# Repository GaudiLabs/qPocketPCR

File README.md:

# qPocketPCR
Quantitative PCR machine detecting fluorescence using a camera

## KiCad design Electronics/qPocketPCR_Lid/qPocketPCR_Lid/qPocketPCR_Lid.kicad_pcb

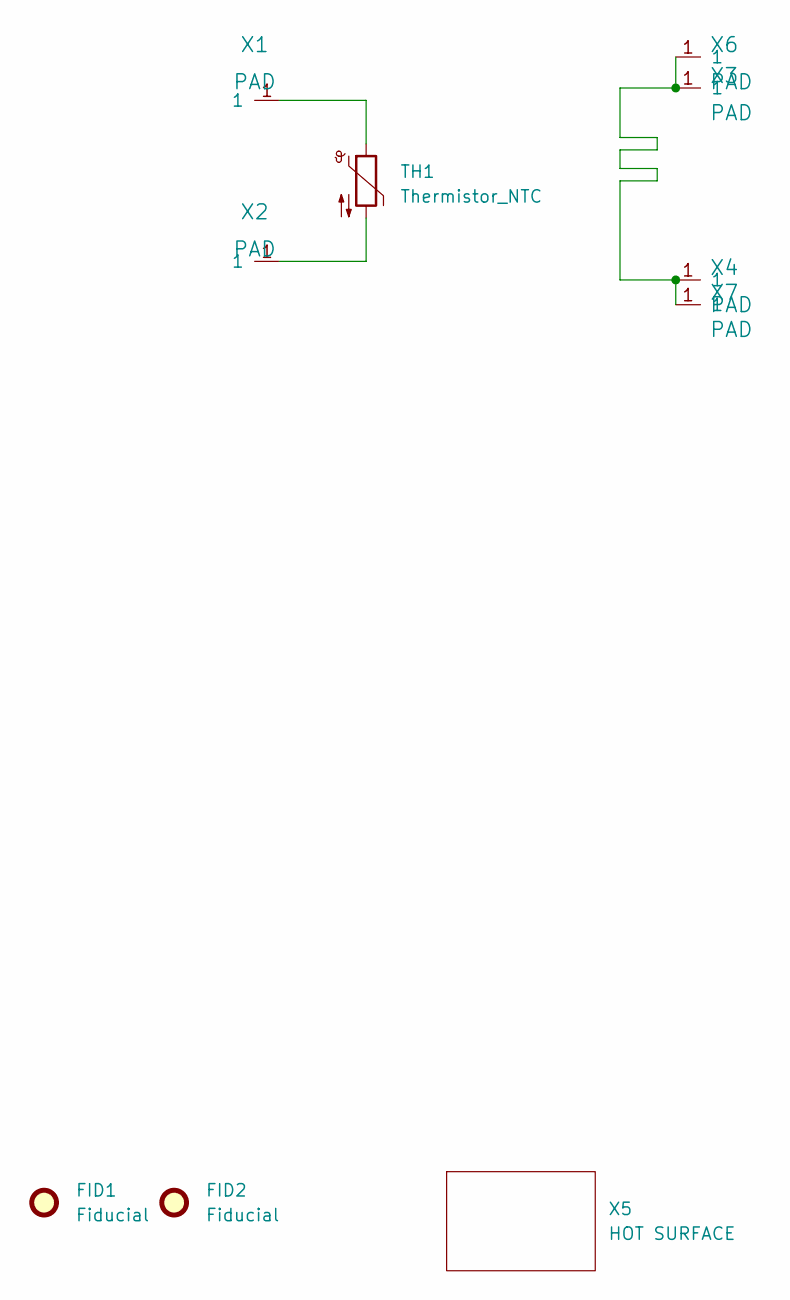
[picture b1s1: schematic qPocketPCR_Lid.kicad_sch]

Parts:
FID1, FID2: Fiducial; Fiducial_0.5mm_Mask1mm
TH1: Thermistor_NTC; R_0402_1005Metric
X1, X2, X3, X4, X6, X7: PAD; PAD_SMD_FFC
X5: HOT SURFACE; HotSurfaceWarning

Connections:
unnamed: TH1.1, X1.1
unnamed: TH1.2, X2.1
unnamed: X3.1, X4.1, X6.1, X7.1

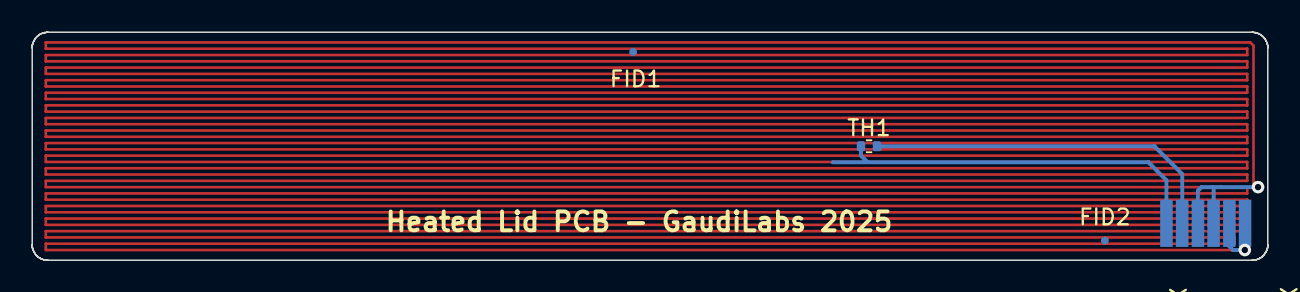
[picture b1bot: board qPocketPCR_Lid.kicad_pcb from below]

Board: 2 copper layers, 78.6 x 14.5 mm, 10 parts (9 on the bottom side), 3 nets.

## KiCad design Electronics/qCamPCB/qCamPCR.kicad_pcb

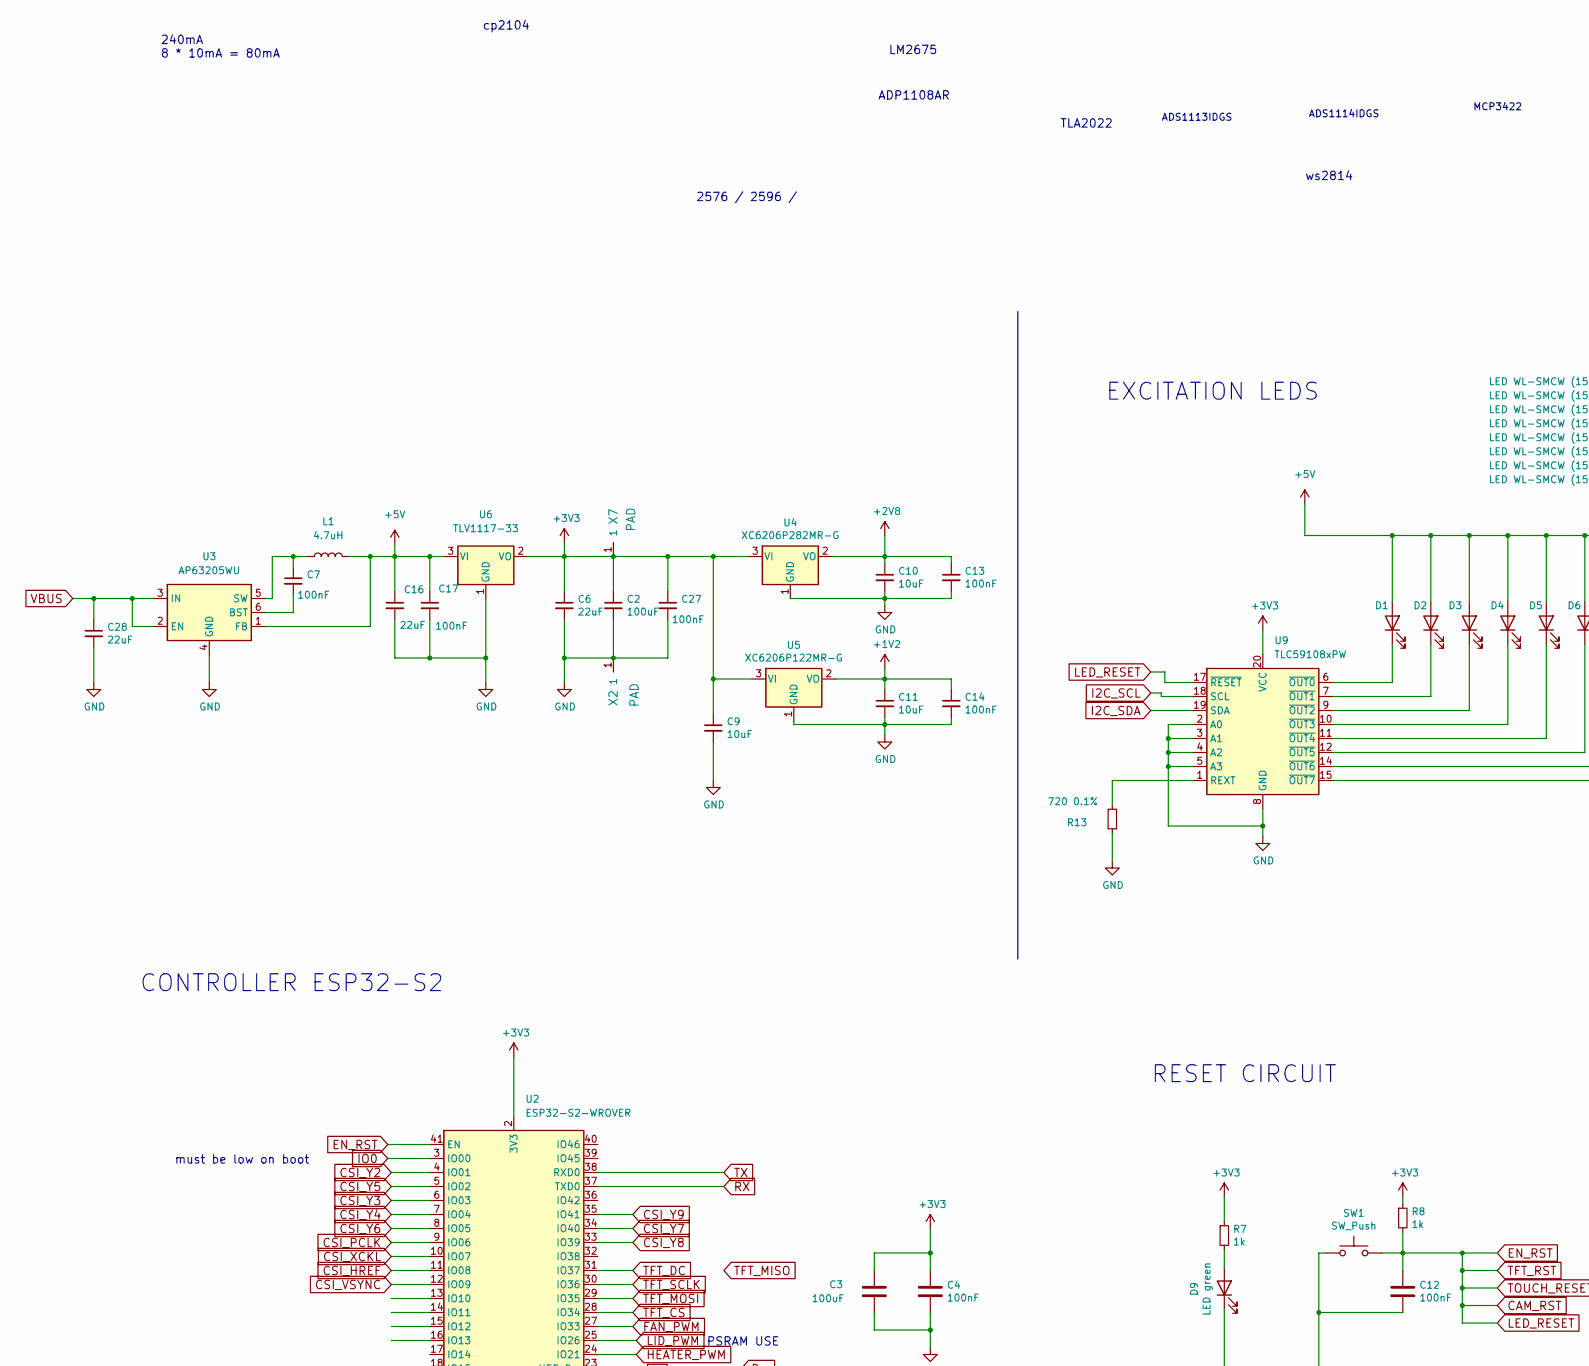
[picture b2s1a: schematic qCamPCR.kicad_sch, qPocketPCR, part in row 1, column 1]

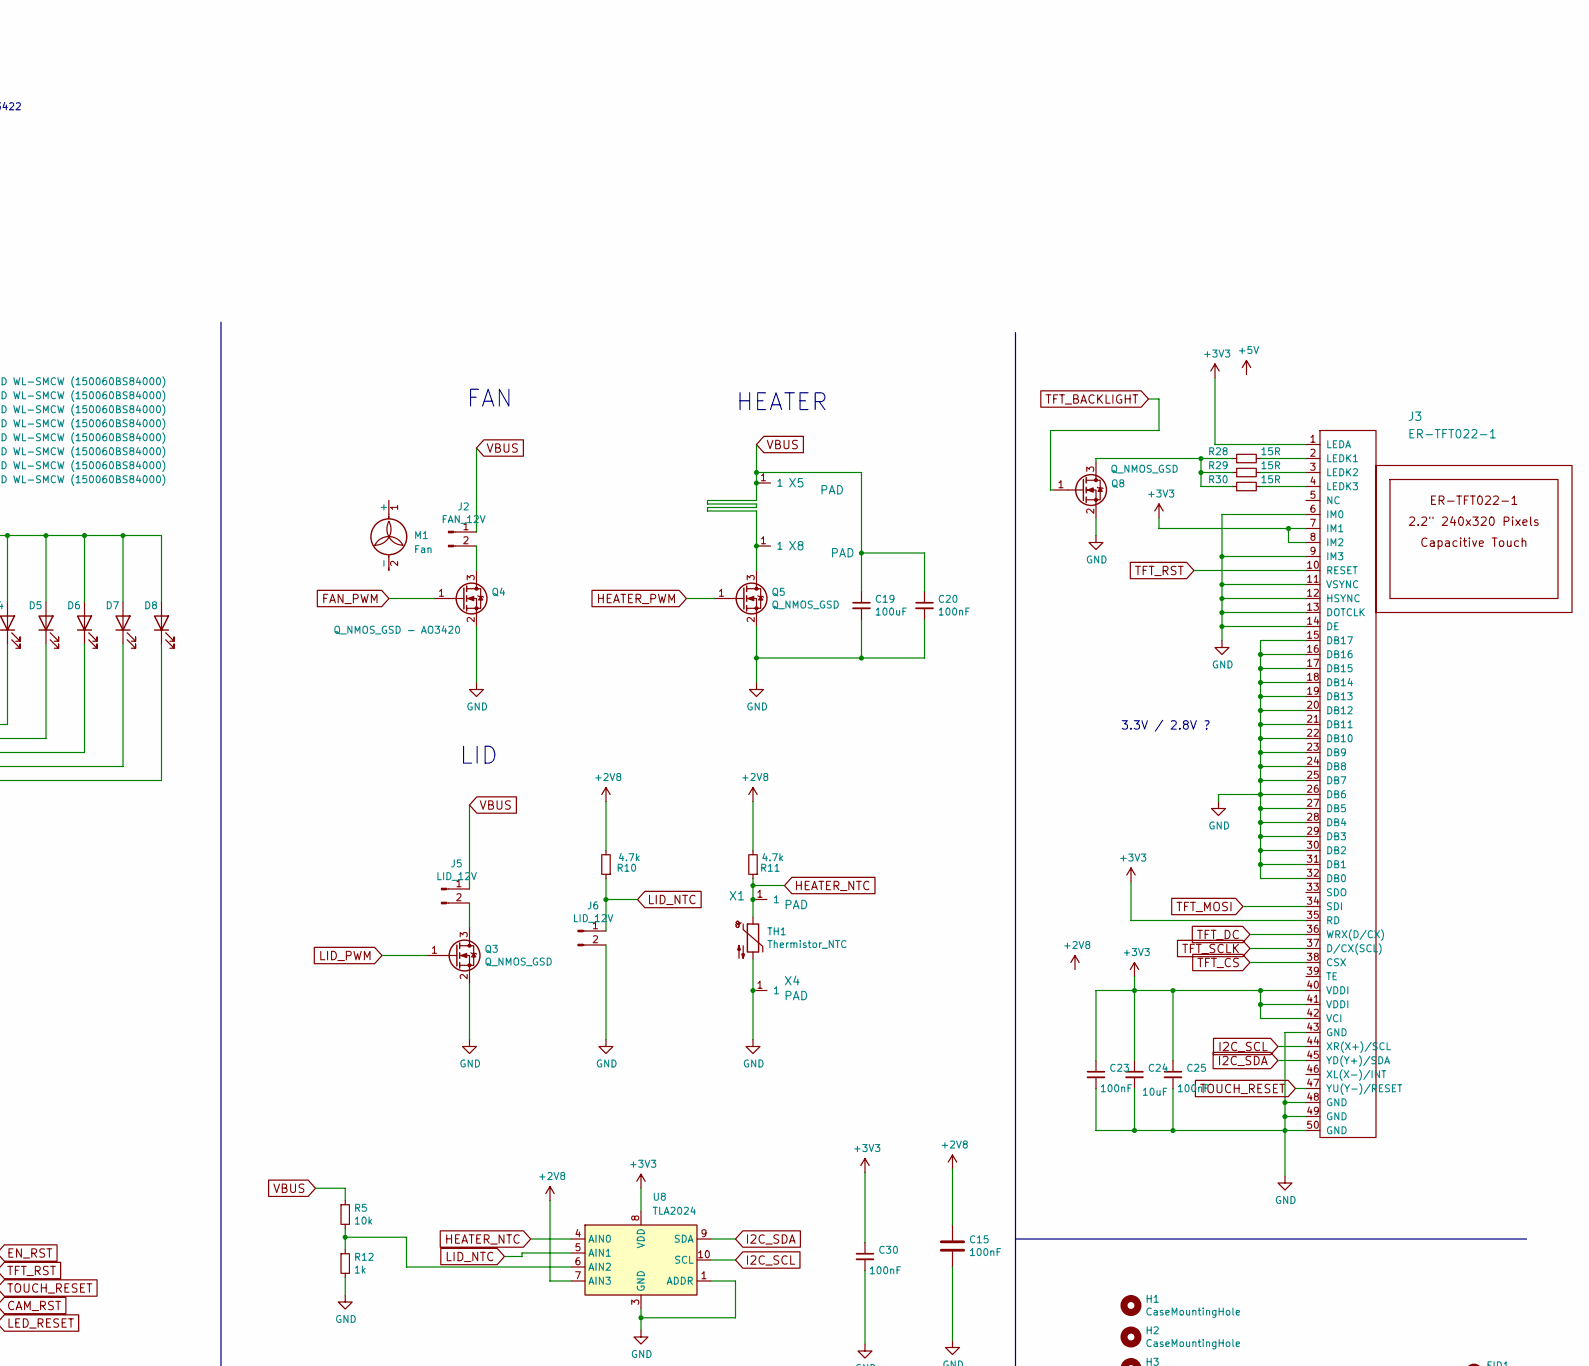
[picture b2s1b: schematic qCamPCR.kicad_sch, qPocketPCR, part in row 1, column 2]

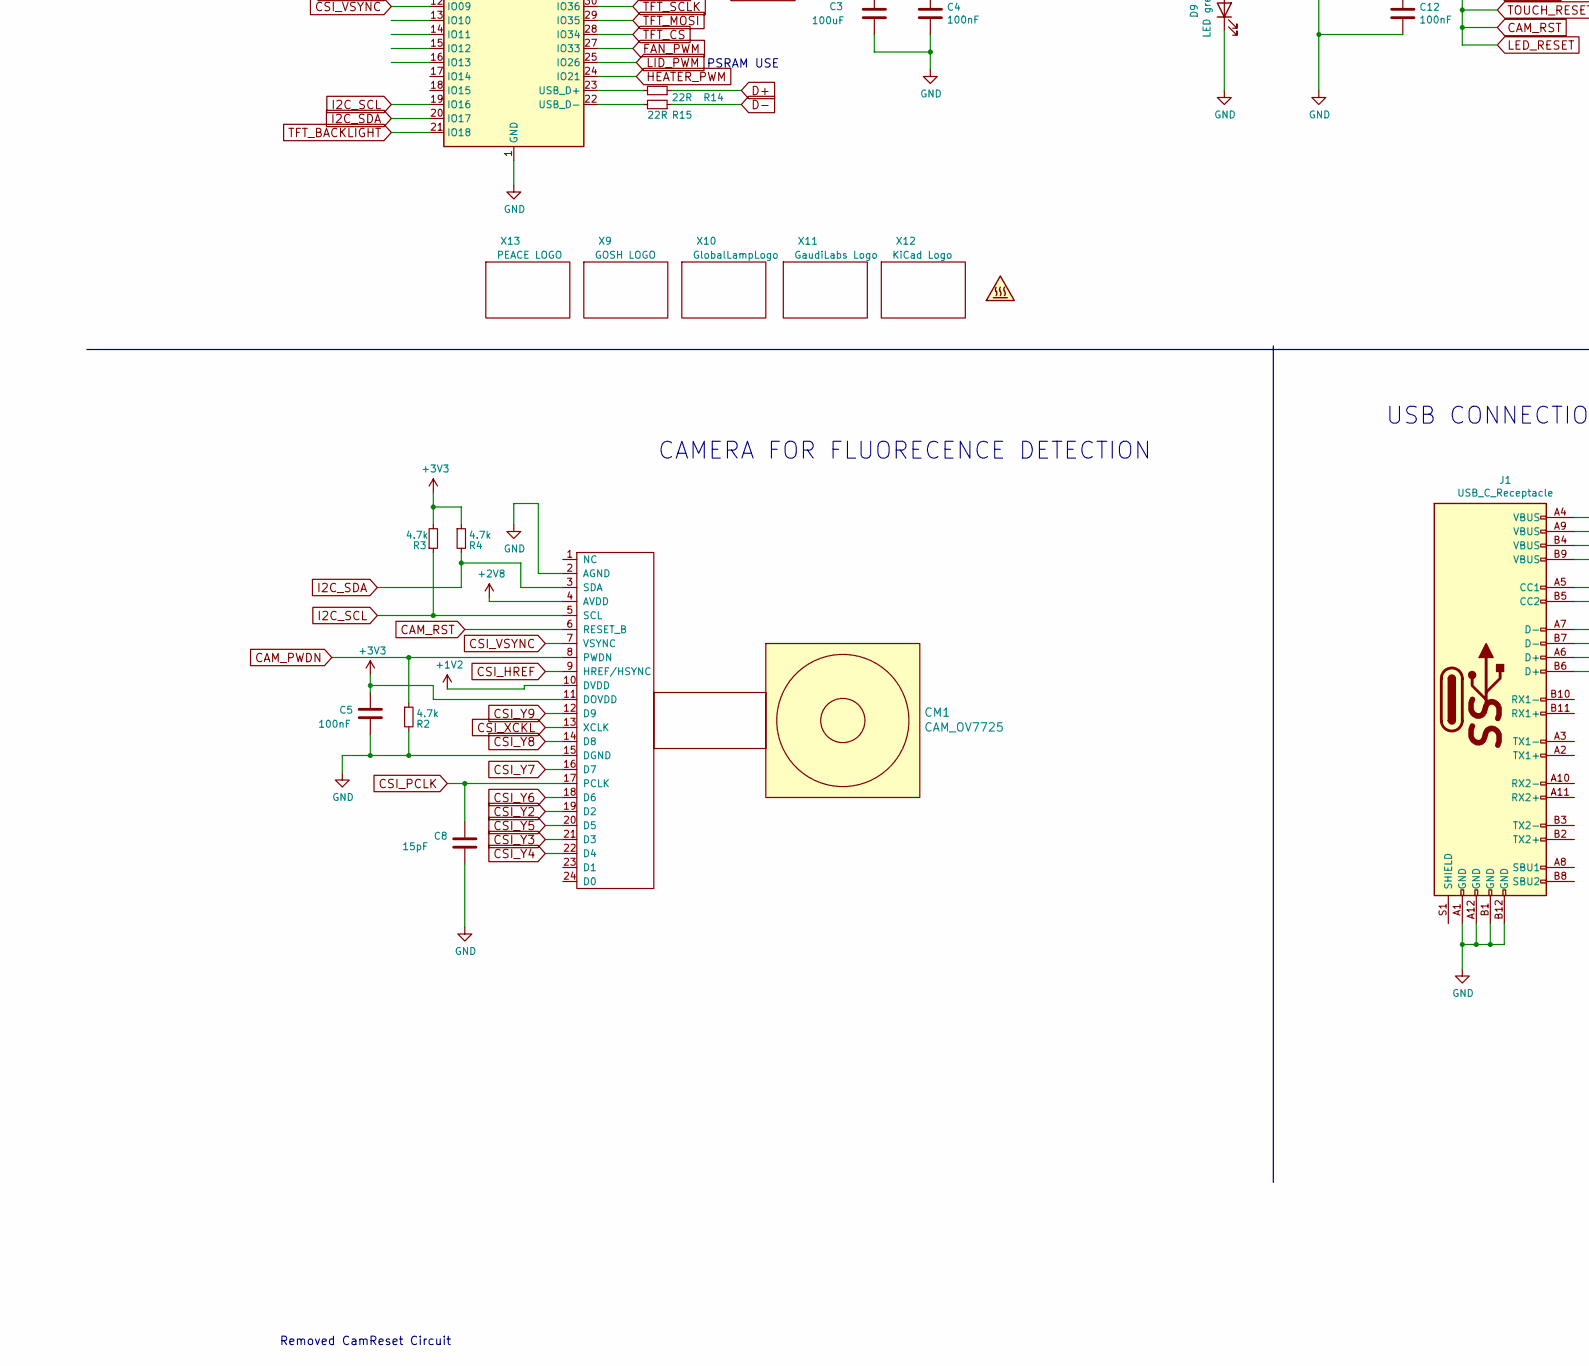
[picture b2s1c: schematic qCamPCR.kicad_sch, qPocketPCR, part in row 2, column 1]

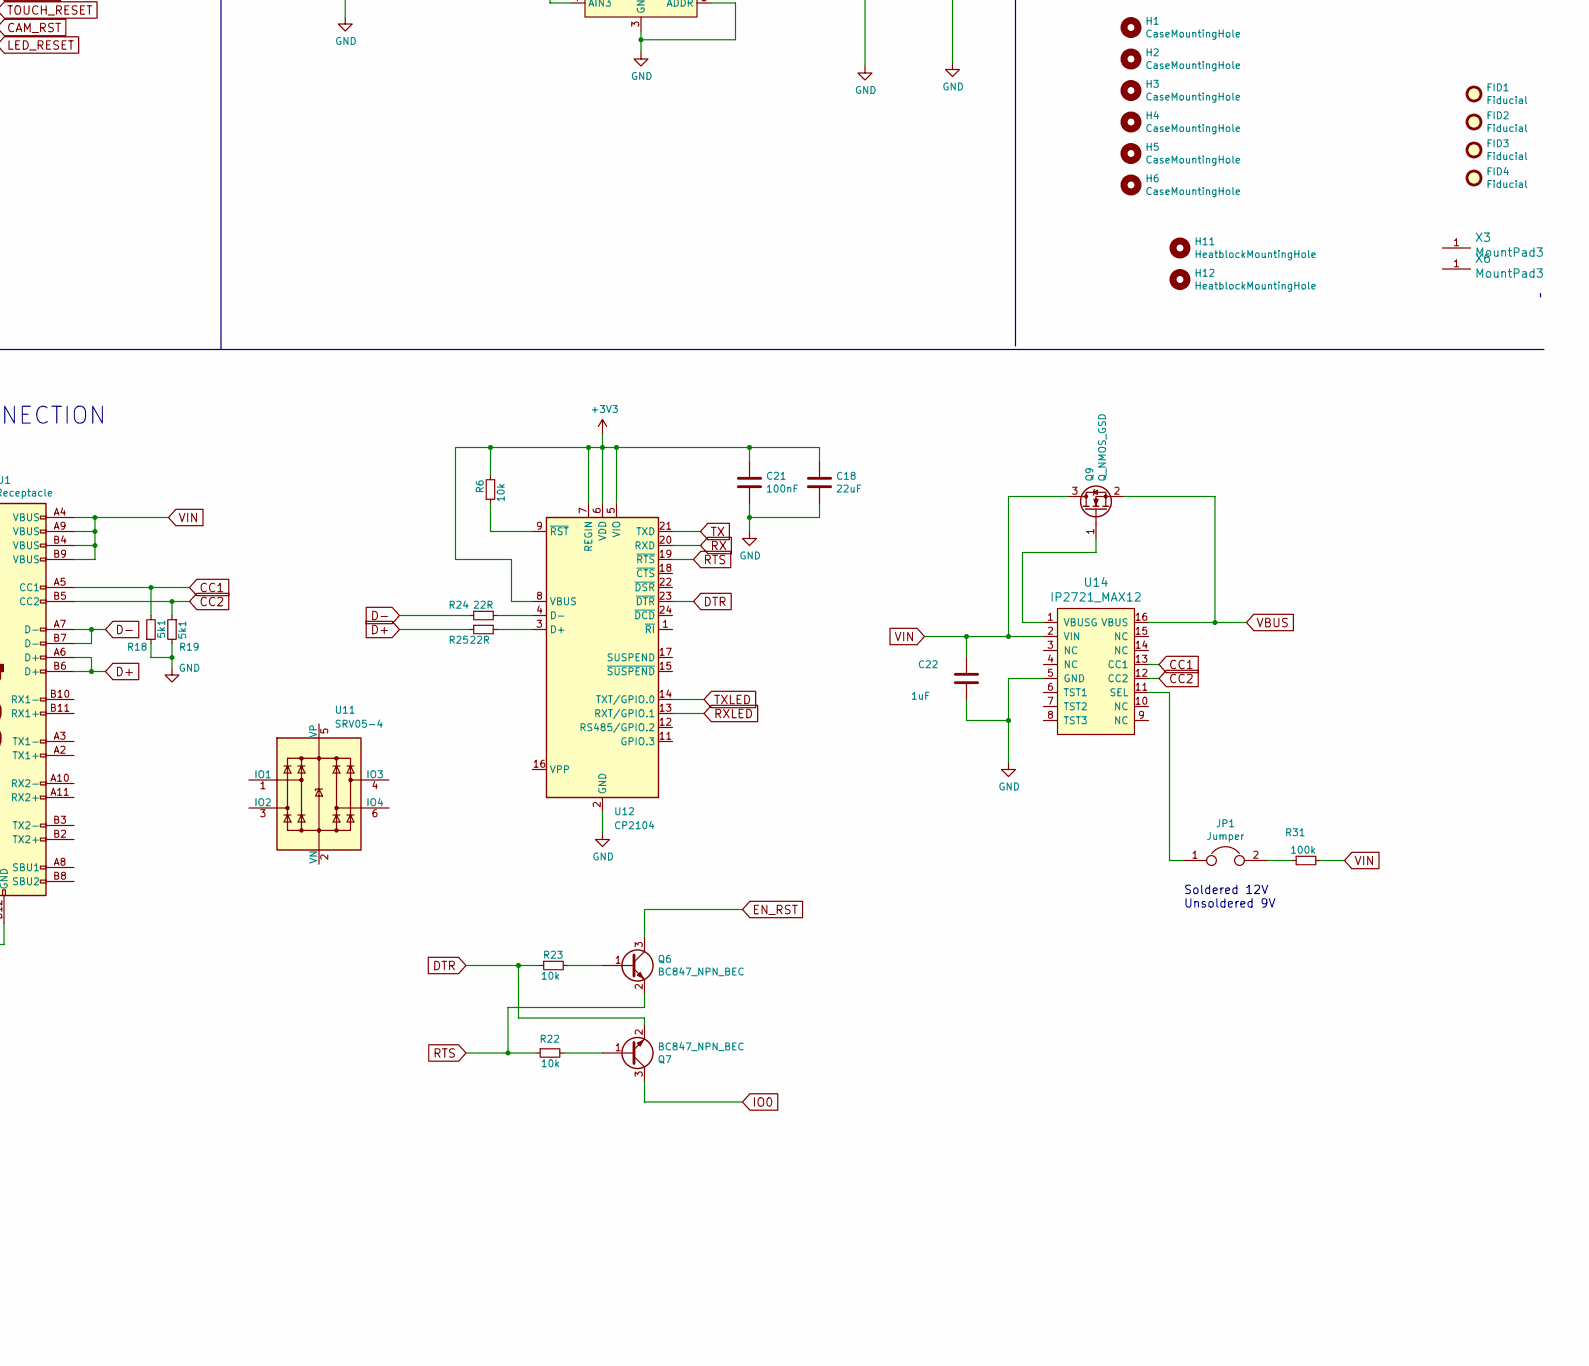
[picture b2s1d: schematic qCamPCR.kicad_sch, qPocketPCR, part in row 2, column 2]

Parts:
C2, C3, C19: 100uF; C_1206_3216Metric
C4, C5, C7, C12, C13, C14, C15, C17, C20, C21, C23, C25, C27, C30: 100nF; C_0603_1608Metric
C6, C16, C18, C28: 22uF; C_0805_2012Metric
C8: 15pF; C_0603_1608Metric
C9, C10, C11, C24: 10uF; C_0805_2012Metric
C22: 1uF; C_0603_1608Metric
CM1: CAM_OV7725; FFC_MOLEX_EASYON_05mm_24_INVERTED
D1, D2, D3, D4, D5, D6, D7, D8: LED WL-SMCW (150060BS84000); LED_SMD_WL-SMCW
D9: LED green; LED_0603_1608Metric
FID1, FID2, FID3, FID4: Fiducial; Fiducial_1mm_Dia_2.54mm_Outer_CopperBottom
H1, H2, H3, H4, H5, H6: CaseMountingHole; MountingHole_3.2mm_M3
H11, H12: HeatblockMountingHole; MountingHole_2.6mm
J1: USB_C_Receptacle; USB_C_Receptacle_Amphenol_12401610E4-2A
J2: FAN_12V; JSP_PH_20_SMD_RIGHT_ANGLE
J3: ER-TFT022-1; ER-TFT022_1
J5, J6: LID_12V; PinHeader_JST_1x02_P2.54mm_Vertical
JP1: Jumper; SolderJumper-2_P1.3mm_Open_RoundedPad1.0x1.5mm
L1: 4.7uH; L_Vishay_IFSC-1515AH_4x4x1.8mm
M1: Fan; 4010FanRadial
Q3, Q5, Q8, Q9: Q_NMOS_GSD; SOT-23
Q4: Q_NMOS_GSD - AO3420; SOT-23
Q6, Q7: BC847_NPN_BEC; SOT-23
R2, R3, R4, R10, R11: 4.7k; R_0603_1608Metric
R5, R6, R22, R23: 10k; R_0603_1608Metric
R7, R8, R12: 1k; R_0603_1608Metric
R13: 720 0.1%; R_0603_1608Metric
R14, R15, R24, R25: 22R; R_0603_1608Metric
R18, R19: 5k1; R_0603_1608Metric
R28, R29, R30: 15R; R_0603_1608Metric
R31: 100k; R_0603_1608Metric
SW1: SW_Push; SW_SPST_KMS221GLFS
TH1: Thermistor_NTC; C_0402_1005Metric
U2: ESP32-S2-WROVER
U3: AP63205WU; TSOT-23-6
U4: XC6206P282MR-G; SOT-23
U5: XC6206P122MR-G; SOT-23
U6: TLV1117-33; SOT-223
U8: TLA2024; Texas_R-PUQFN-N10
U9: TLC59108xPW; TSSOP-20_4.4x6.5mm_P0.65mm
U11: SRV05-4; SOT-23-6
U12: CP2104; QFN-24-1EP_4x4mm_P0.5mm_EP2.6x2.6mm
U14: IP2721_MAX12; TSSOP-16_4.4x5mm_P0.65mm
X1, X2, X4, X5, X7, X8: PAD; PAD_SMD_3mm
X3, X6: MountPad3; PAD_SMD_2x1mm
X9: GOSH LOGO; GOSH_Logo_21mm
X10: GlobalLampLogo
X11: GaudiLabs Logo; GaudiLabs_12
X12: KiCad Logo; KiCad-Logo2_5mm_SilkScreen
X13: PEACE LOGO; Peace_logo

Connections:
+1V2: C11.1, C14.1, CM1.10 (DVDD), U5.2 (VO)
+2V8: C10.1, C13.1, C15.1, CM1.4 (AVDD), R10.2, R11.2, U4.2 (VO), U8.7 (AIN3)
+3V3: C2.1, C3.1, C4.1, C5.1, C6.1, C9.1, C18.1, C21.1, C23.1, C24.1, C25.1, C27.1, C30.1, CM1.11 (DOVDD), J3.1 (LEDA), J3.7 (IM1), J3.8 (IM2), J3.35 (RD), J3.40 (VDDI), J3.41 (VDDI), J3.42 (VCI), R3.2, R4.1, R6.2, R7.1, R8.1, U2.2 (3V3), U4.3 (VI), U5.3 (VI), U6.2 (VO), U8.8 (VDD), U9.20 (VCC), U12.5 (VIO), U12.6 (VDD), U12.7 (REGIN), U12.8 (VBUS), X7.1
+5V: C16.1, C17.1, D1.2 (A), D2.2 (A), D3.2 (A), D4.2 (A), D5.2 (A), D6.2 (A), D7.2 (A), D8.2 (A), L1.2, U3.1 (FB), U6.3 (VI)
CAM_PWDN: CM1.8 (PWDN), R2.1
CAM_RST: C12.1, CM1.6 (RESET_B), J3.10 (RESET), J3.47 (YU(Y-)/RESET), Q6.3 (C), R8.2, SW1.2, U2.41 (EN), U9.17 (~RESET)
CC1: J1.A5 (CC1), R18.2, U14.13 (CC1)
CC2: J1.B5 (CC2), R19.1, U14.12 (CC2)
CSI_HREF: CM1.9 (HREF/HSYNC), U2.11 (IO08)
CSI_PCLK: C8.1, CM1.17 (PCLK), U2.9 (IO06)
CSI_VSYNC: CM1.7 (VSYNC), U2.12 (IO09)
CSI_XCKL: CM1.13 (XCLK), U2.10 (IO07)
CSI_Y2: CM1.19 (D2), U2.4 (IO01)
CSI_Y3: CM1.21 (D3), U2.6 (IO03)
CSI_Y4: CM1.22 (D4), U2.7 (IO04)
CSI_Y5: CM1.20 (D5), U2.5 (IO02)
CSI_Y6: CM1.18 (D6), U2.8 (IO05)
CSI_Y7: CM1.16 (D7), U2.34 (IO40)
CSI_Y8: CM1.14 (D8), U2.33 (IO39)
CSI_Y9: CM1.12 (D9), U2.35 (IO41)
D+: J1.A6 (D+), J1.B6 (D+), R14.1, R25.1
D-: J1.A7 (D-), J1.B7 (D-), R15.1, R24.1
DTR: Q7.2 (E), R23.1, U12.23 (~DTR)
FAN_PWM: Q4.1 (G), U2.27 (IO33)
GND: C2.2, C3.2, C4.2, C5.2, C6.2, C8.2, C9.2, C10.2, C11.2, C12.2, C13.2, C14.2, C15.2, C16.2, C17.2, C18.2, C19.2, C20.2, C21.2, C22.2, C23.2, C24.2, C25.2, C27.2, C28.2, C30.2, CM1.2 (AGND), CM1.15 (DGND), D9.1 (K), J1.A1 (GND), J1.A12 (GND), J1.B1 (GND), J1.B12 (GND), J3.6 (IM0), J3.9 (IM3), J3.11 (VSYNC), J3.12 (HSYNC), J3.13 (DOTCLK), J3.14 (DE), J3.15 (DB17), J3.16 (DB16), J3.17 (DB15), J3.18 (DB14), J3.19 (DB13), J3.20 (DB12), J3.21 (DB11), J3.22 (DB10), J3.23 (DB9), J3.24 (DB8), J3.25 (DB7), J3.26 (DB6), J3.27 (DB5), J3.28 (DB4), J3.29 (DB3), J3.30 (DB2), J3.31 (DB1), J3.32 (DB0), J3.43 (GND), J3.48 (GND), J3.49 (GND), J3.50 (GND), J6.2, Q3.2 (S), Q4.2 (S), Q5.2 (S), Q8.2 (S), R2.2, R12.2, R13.1, R18.1, R19.2, SW1.1, TH1.2, U2.1 (GND), U2.26 (GND), U2.42 (GND), U2.43 (GND), U3.4 (GND), U4.1 (GND), U5.1 (GND), U6.1 (GND), U8.1 (ADDR), U8.3 (GND), U9.2 (A0), U9.3 (A1), U9.4 (A2), U9.5 (A3), U9.8 (GND), U9.13 (GND), U9.16 (GND), U12.2 (GND), U12.25 (GND), U14.5 (GND), X2.1, X4.1
HEATER_NTC: R11.1, TH1.1, U8.4 (AIN0), X1.1
HEATER_PWM: Q5.1 (G), U2.24 (IO21)
I2C_SCL: CM1.5 (SCL), J3.44 (XR(X+)/SCL), R3.1, U2.19 (IO16), U8.10 (SCL), U9.18 (SCL)
I2C_SDA: CM1.3 (SDA), J3.45 (YD(Y+)/SDA), R4.2, U2.20 (IO17), U8.9 (SDA), U9.19 (SDA)
IO0: Q7.3 (C), U2.3 (IO00)
LID_NTC: J6.1, R10.1, U8.5 (AIN1)
LID_PWM: Q3.1 (G), U2.25 (IO26)
unnamed: C7.1, L1.1, U3.5 (SW)
unnamed: C7.2, U3.6 (BST)
unnamed: D1.1 (K), U9.6 (~OUT0)
unnamed: D2.1 (K), U9.7 (~OUT1)
unnamed: D3.1 (K), U9.9 (~OUT2)
unnamed: D4.1 (K), U9.10 (~OUT3)
unnamed: D5.1 (K), U9.11 (~OUT4)
unnamed: D6.1 (K), U9.12 (~OUT5)
unnamed: D7.1 (K), U9.14 (~OUT6)
unnamed: D8.1 (K), U9.15 (~OUT7)
unnamed: D9.2 (A), R7.2
unnamed: J2.2, Q4.3 (D)
unnamed: J3.2 (LEDK1), R28.2
unnamed: J3.3 (LEDK2), R29.2
unnamed: J3.4 (LEDK3), R30.2
unnamed: J5.2, Q3.3 (D)
unnamed: JP1.1, U14.11 (SEL)
unnamed: JP1.2, R31.1
unnamed: Q6.1 (B), R23.2
unnamed: Q7.1 (B), R22.2
unnamed: Q8.3 (D), R28.1, R29.1, R30.1
unnamed: Q9.1 (G), U14.1 (VBUSG)
unnamed: R6.1, U12.9 (~RST)
unnamed: R5.2, R12.1, U8.6 (AIN2)
unnamed: R13.2, U9.1 (REXT)
unnamed: R14.2, U2.23 (USB_D+)
unnamed: R15.2, U2.22 (USB_D-)
unnamed: R24.2, U12.4 (D-)
unnamed: R25.2, U12.3 (D+)
RTS: Q6.2 (E), R22.1, U12.19 (~RTS)
RX: U2.37 (TXD0), U12.20 (RXD)
RXLED: U12.13 (RXT/GPIO.1)
TFT_BACKLIGHT: Q8.1 (G), U2.21 (IO18)
TFT_CS: J3.38 (CSX), U2.28 (IO34)
TFT_DC: J3.36 (WRX(D/CX)), U2.31 (IO37)
TFT_MOSI: J3.34 (SDI), U2.29 (IO35)
TFT_SCLK: J3.37 (D/CX(SCL)), U2.30 (IO36)
TX: U2.38 (RXD0), U12.21 (TXD)
TXLED: U12.14 (TXT/GPIO.0)
VBUS: C19.1, C20.1, C28.1, J2.1, J5.1, Q5.3 (D), Q9.2 (S), R5.1, U3.2 (EN), U3.3 (IN), U14.16 (VBUS), X5.1, X8.1
VIN: C22.1, J1.A4 (VBUS), J1.A9 (VBUS), J1.B4 (VBUS), J1.B9 (VBUS), Q9.3 (D), R31.2, U14.2 (VIN)

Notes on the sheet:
LID
RESET CIRCUIT
ADS1113IDGS
Soldered 12V Unsoldered 9V
LM2675
3.3V / 2.8V ?
HEATER
MCP3422
2576 / 2596 /
PSRAM USE
cp2104
CAMERA FOR FLUORECENCE DETECTION
EXCITATION LEDS
USB CONNECTION
Removed CamReset Circuit
240mA 8 * 10mA = 80mA
ADP1108AR
TLA2022
FAN
ws2814
ADS1114IDGS
CONTROLLER ESP32-S2
must be low on boot

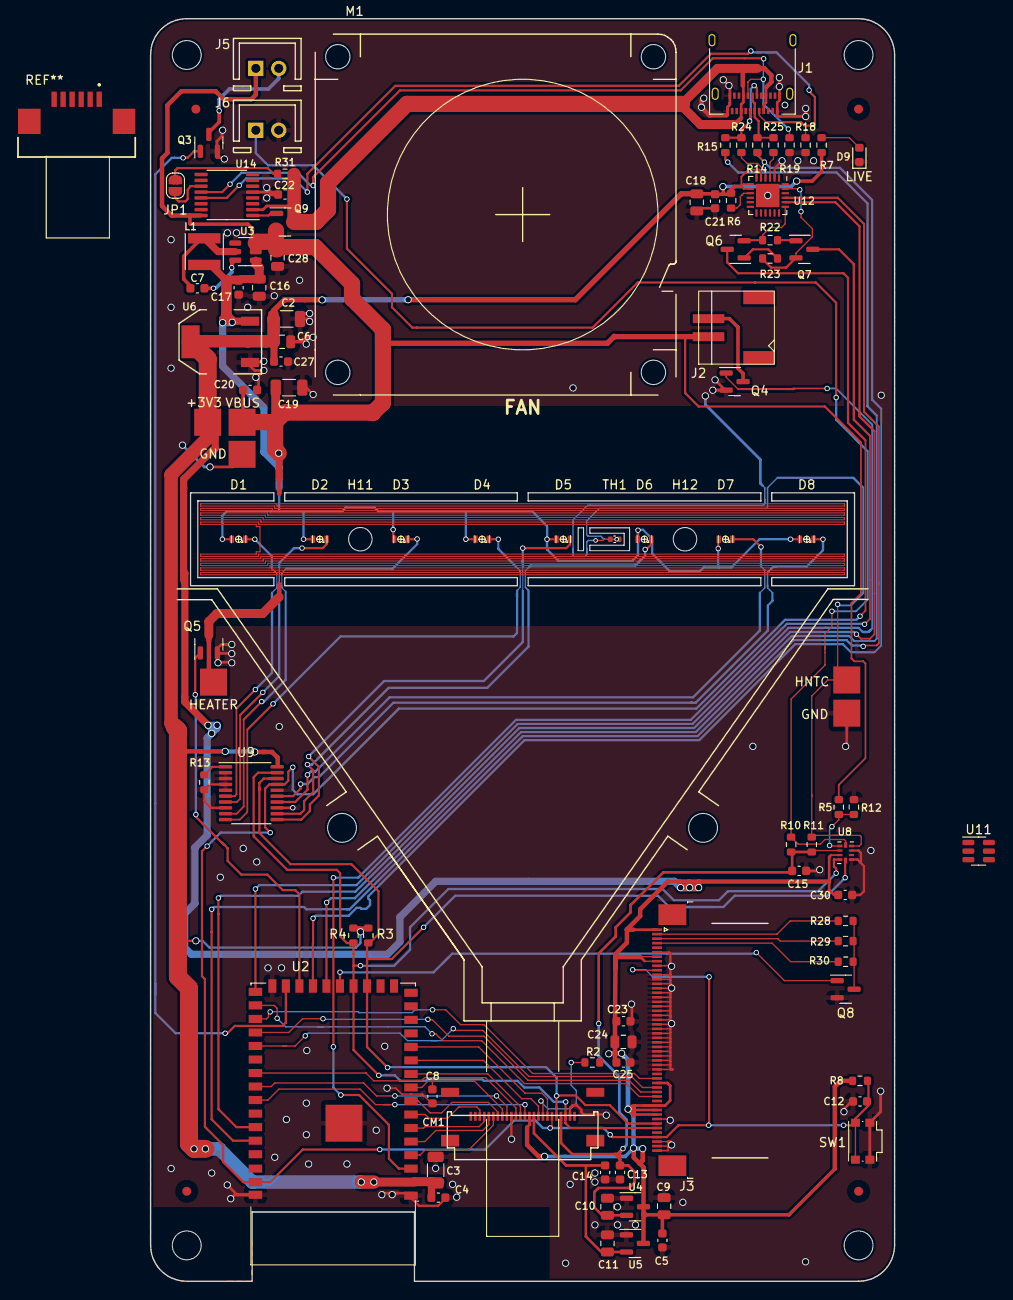
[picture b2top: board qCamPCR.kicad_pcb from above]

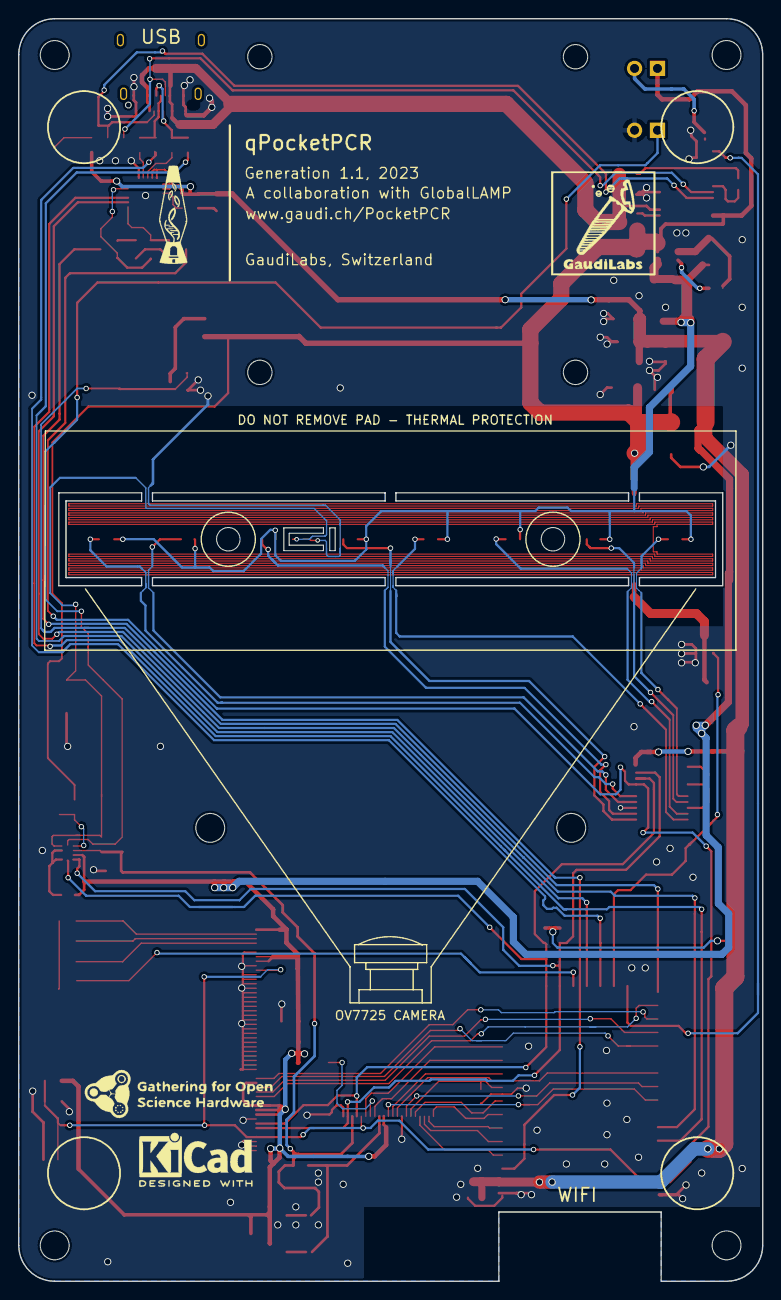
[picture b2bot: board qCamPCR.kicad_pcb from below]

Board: 2 copper layers, 82.5 x 140.0 mm, 112 parts (4 on the bottom side), 71 nets.

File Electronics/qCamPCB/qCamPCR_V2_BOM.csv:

"Id";"Designator";"Package";"Quantity";"Designation";"Supplier and ref";
1;"CM1";"FFC_MOLEX_EASYON_05mm_24_INVERTED";1;"CAM_OV7725";;;
2;"J1";"USB_C_Receptacle_Amphenol_12401610E4-2A";1;"USB_C_Receptacle";;;
3;"J3";"ER-TFT022_1";1;"ER-TFT022-1";;;
4;"U5";"SOT-23";1;"XC6206P122MR-G";;;
5;"D1,D2,D3,D4,D5,D7,D6,D8";"LED_SMD_WL-SMCW";8;"LED WL-SMCW (150060BS84000)";;;
6;"R2,R3,R10,R11,R4";"R_0603_1608Metric";5;"4.7k";;;
7;"R7,R8,R5,R12";"R_0603_1608Metric";4;"1k";;;
8;"R28,R29,R30";"R_0603_1608Metric";3;"15R";;;
9;"R24,R25,R14,R15";"R_0603_1608Metric";4;"22R";;;
10;"R18,R19";"R_0603_1608Metric";2;"5k1";;;
11;"R31";"R_0603_1608Metric";1;"100k";;;
12;"U4";"SOT-23";1;"XC6206P282MR-G";;;
13;"H1,H2,H3,H4,H5,H6";"MountingHole_3.2mm_M3";6;"CaseMountingHole";;;
14;"FID1,FID2,FID4,FID3";"Fiducial_1mm_Dia_2.54mm_Outer_CopperBottom";4;"Fiducial";;;
15;"C2,C3,C19";"C_1206_3216Metric";3;"100uF";;;
16;"C4,C5,C7,C12,C13,C15,C20,C21,C23,C25,C27,C14,C30,C17";"C_0603_1608Metric";14;"100nF";;;
17;"C6,C28,C18,C16";"C_0805_2012Metric";4;"22uF";;;
18;"C8";"C_0603_1608Metric";1;"15pF";;;
19;"C9,C10,C11,C24";"C_0805_2012Metric";4;"10uF";;;
20;"J6,J5";"PinHeader_JST_1x02_P2.54mm_Vertical";2;"LID_12V";;;
21;"Q3,Q4,Q5,Q8,Q9";"SOT-23";5;"Q_NMOS_GSD";;;
22;"J2";"JSP_PH_20_SMD_RIGHT_ANGLE";1;"FAN_12V";;;
23;"D9";"LED_0603_1608Metric";1;"LED green";;;
24;"R23,R22,R6";"R_0603_1608Metric";3;"10k";;;
25;"Q6,Q7";"SOT-23";2;"BC847_NPN_BEC";;;
26;"JP1";"SolderJumper-2_P1.3mm_Open_RoundedPad1.0x1.5mm";1;"Jumper";;;
27;"SW1";"SW_SPST_KMS221GLFS";1;"SW_Push";;;
28;"X1,X4,X5,X7,X2,X8";"PAD_SMD_3mm";6;"PAD";;;
29;"H12,H11";"MountingHole_2.6mm";2;"HeatblockMountingHole";;;
30;"TH1";"C_0402_1005Metric";1;"Thermistor_NTC";;;
31;"C22";"C_0603_1608Metric";1;"1uF";;;
32;"X3,X6";"PAD_SMD_2x1mm";2;"MountPad3";;;
33;"U14";"TSSOP-16_4.4x5mm_P0.65mm";1;"IP2721_MAX12";;;
34;"U2";"ESP32-S2-WROVER";1;"ESP32-S2-WROVER";;;
35;"U6";"SOT-223";1;"TLV1117-33";;;
36;"U3";"TSOT-23-6";1;"AP63205WU";;;
37;"U12";"QFN-24-1EP_4x4mm_P0.5mm_EP2.6x2.6mm";1;"CP2104";;;
38;"U8";"Texas_R-PUQFN-N10";1;"TLA2024";;;
39;"L1";"L_Vishay_IFSC-1515AH_4x4x1.8mm";1;"4.7uH";;;
40;"X13";"Peace_logo";1;"PEACE LOGO";;;
41;"R13";"R_0603_1608Metric";1;"720 0.1%";;;
42;"U9";"TSSOP-20_4.4x6.5mm_P0.65mm";1;"TLC59108xPW";;;
43;"M1";"4010FanRadial";1;"Fan";;;
44;"X11";"GaudiLabs_12";1;"GaudiLabs Logo";;;
45;"X9";"GOSH_Logo_21mm";1;"GOSH LOGO";;;
46;"X10";"GlobalLampLogo";1;"GlobalLampLogo";;;
47;"X12";"KiCad-Logo2_5mm_SilkScreen";1;"KiCad Logo";;;

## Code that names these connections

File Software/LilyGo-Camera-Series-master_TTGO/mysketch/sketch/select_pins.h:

/*

 _                      _       _   _
| |                    (_)     | | | |
| |      ___ __      __ _  ___ | |_| |  ___
| |     / _ \\ \ /\ / /| |/ __||  _  | / _ \
| |____|  __/ \ V  V / | |\__ \| | | ||  __/
\_____/ \___|  \_/\_/  |_||___/\_| |_/ \___|

Compatible with all TTGO camera products, written by LewisHe
03/28/2020
*/

#if defined(T_Camera_V16_VERSION)
#define PWDN_GPIO_NUM       -1
#define RESET_GPIO_NUM      -1
#define XCLK_GPIO_NUM       4
#define SIOD_GPIO_NUM       18
#define SIOC_GPIO_NUM       23

#define Y9_GPIO_NUM         36
#define Y8_GPIO_NUM         15
#define Y7_GPIO_NUM         12
#define Y6_GPIO_NUM         39
#define Y5_GPIO_NUM         35
#define Y4_GPIO_NUM         14
#define Y3_GPIO_NUM         13
#define Y2_GPIO_NUM         34

#define VSYNC_GPIO_NUM      5
#define HREF_GPIO_NUM       27
#define PCLK_GPIO_NUM       25

#define AS312_PIN           19
#define BUTTON_1            0

#define I2C_SDA             21
#define I2C_SCL             22

#define SSD130_MODLE_TYPE   0       // 0 : GEOMETRY_128_64  // 1: GEOMETRY_128_32

#define IIS_SCK             26
#define IIS_WS              32
#define IIS_DOUT            33

#elif defined(T_Camera_V05_VERSION)
#define PWDN_GPIO_NUM       26
#define RESET_GPIO_NUM      -1
#define XCLK_GPIO_NUM       32
#define SIOD_GPIO_NUM       13
#define SIOC_GPIO_NUM       12

#define Y9_GPIO_NUM         39
#define Y8_GPIO_NUM         36
#define Y7_GPIO_NUM         23
#define Y6_GPIO_NUM         18
#define Y5_GPIO_NUM         15
#define Y4_GPIO_NUM         4
#define Y3_GPIO_NUM         14
#define Y2_GPIO_NUM         5

#define VSYNC_GPIO_NUM      27
#define HREF_GPIO_NUM       25
#define PCLK_GPIO_NUM       19

#define AS312_PIN           33
#define BUTTON_1            34

#define I2C_SDA             21
#define I2C_SCL             22

#define SSD130_MODLE_TYPE   0       // 0 : GEOMETRY_128_64  // 1: GEOMETRY_128_32


#elif defined(T_Camera_JORNAL_VERSION)

#define PWDN_GPIO_NUM     -1
#define RESET_GPIO_NUM    15
#define XCLK_GPIO_NUM     27
#define SIOD_GPIO_NUM     25
#define SIOC_GPIO_NUM     23

#define Y9_GPIO_NUM       19
#define Y8_GPIO_NUM       36
#define Y7_GPIO_NUM       18
#define Y6_GPIO_NUM       39
#define Y5_GPIO_NUM       5
#define Y4_GPIO_NUM       34
#define Y3_GPIO_NUM       35
#define Y2_GPIO_NUM       17

#define VSYNC_GPIO_NUM    22
#define HREF_GPIO_NUM     26
#define PCLK_GPIO_NUM     21

#define I2C_SDA           14
#define I2C_SCL           13

#define BUTTON_1          32

#define SSD130_MODLE_TYPE   1   // 0 : GEOMETRY_128_64  // 1: GEOMETRY_128_32

#elif defined(T_Camera_PLUS_VERSION)
#define PWDN_GPIO_NUM       -1
#define RESET_GPIO_NUM      -1
#define XCLK_GPIO_NUM       4
#define SIOD_GPIO_NUM       18
#define SIOC_GPIO_NUM       23

#define Y9_GPIO_NUM         36
#define Y8_GPIO_NUM         37
#define Y7_GPIO_NUM         38
#define Y6_GPIO_NUM         39
#define Y5_GPIO_NUM         35
#define Y4_GPIO_NUM         26
#define Y3_GPIO_NUM         13
#define Y2_GPIO_NUM         34
#define VSYNC_GPIO_NUM      5
#define HREF_GPIO_NUM       27
#define PCLK_GPIO_NUM       25

#define I2C_SDA             18
#define I2C_SCL             23

#define IIS_SCK             14
#define IIS_WS              32
#define IIS_DOUT            33

#define TFT_CS_PIN          12
#define TFT_DC_PIN          15
#define TFT_MOSI_PIN        19
#define TFT_MISO_PIN        22
#define TFT_SCLK_PIN        21
#define TFT_BL_PIN          2

#define SDCARD_CS_PIN       0

#define ENABLE_IP5306
#define ENABLE_TFT

#elif defined(T_Camera_V162_VERSION)

#define PWDN_GPIO_NUM       -1
#define RESET_GPIO_NUM      -1
#define XCLK_GPIO_NUM       4
#define SIOD_GPIO_NUM       18
#define SIOC_GPIO_NUM       23

#define Y9_GPIO_NUM         36
#define Y8_GPIO_NUM         37
#define Y7_GPIO_NUM         38
#define Y6_GPIO_NUM         39
#define Y5_GPIO_NUM         35
#define Y4_GPIO_NUM         14
#define Y3_GPIO_NUM         13
#define Y2_GPIO_NUM         34
#define VSYNC_GPIO_NUM      5
#define HREF_GPIO_NUM       27
#define PCLK_GPIO_NUM       25

#define I2C_SDA             21
#define I2C_SCL             22

#define BUTTON_1            15

#define SSD130_MODLE_TYPE   0   // 0 : GEOMETRY_128_64  // 1: GEOMETRY_128_32

#define AS312_PIN           19  //not rtc io ,can't form deepsleep wakeup

#define IIS_SCK             26
#define IIS_WS              32
#define IIS_DOUT            33

#define ENABLE_IP5306

#elif defined(T_Camera_MINI_VERSION)

#define PWDN_GPIO_NUM    -1
#define RESET_GPIO_NUM   -1
#define XCLK_GPIO_NUM    32
#define SIOD_GPIO_NUM    13
#define SIOC_GPIO_NUM    12

#define Y9_GPIO_NUM      39
#define Y8_GPIO_NUM      36
#define Y7_GPIO_NUM      38
#define Y6_GPIO_NUM      37
#define Y5_GPIO_NUM      15
#define Y4_GPIO_NUM      4
#define Y3_GPIO_NUM      14
#define Y2_GPIO_NUM      5

#define VSYNC_GPIO_NUM   27
#define HREF_GPIO_NUM    25
#define PCLK_GPIO_NUM    19
#define CAMERA_PWR_PIN   26

#define I2C_SDA             21
#define I2C_SCL             22

#define BUTTON_1            33

#define POWER_CONTROL_PIN     26

#define ENABLE_AXP192
#elif defined(T_Camera_V17_VERSION)

#define PWDN_GPIO_NUM       -1
#define RESET_GPIO_NUM      -1
#define XCLK_GPIO_NUM       32
#define SIOD_GPIO_NUM       13
#define SIOC_GPIO_NUM       12

#define Y9_GPIO_NUM         39
#define Y8_GPIO_NUM         36
#define Y7_GPIO_NUM         23
#define Y6_GPIO_NUM         18
#define Y5_GPIO_NUM         15
#define Y4_GPIO_NUM         4
#define Y3_GPIO_NUM         14
#define Y2_GPIO_NUM         5

#define VSYNC_GPIO_NUM      27
#define HREF_GPIO_NUM       25
#define PCLK_GPIO_NUM       19

#define I2C_SDA             21
#define I2C_SCL             22

#define BUTTON_1            34

#define SSD130_MODLE_TYPE   0   // 0 : GEOMETRY_128_64  // 1: GEOMETRY_128_32

#define AS312_PIN           33

#define ENABLE_IP5306

#elif defined(ESPRESSIF_ESP_EYE)
#define PWDN_GPIO_NUM    -1
#define RESET_GPIO_NUM   -1
#define XCLK_GPIO_NUM    4
#define SIOD_GPIO_NUM    18
#define SIOC_GPIO_NUM    23

#define Y9_GPIO_NUM      36
#define Y8_GPIO_NUM      37
#define Y7_GPIO_NUM      38
#define Y6_GPIO_NUM      39
#define Y5_GPIO_NUM      35
#define Y4_GPIO_NUM      14
#define Y3_GPIO_NUM      13
#define Y2_GPIO_NUM      34
#define VSYNC_GPIO_NUM   5
#define HREF_GPIO_NUM    27
#define PCLK_GPIO_NUM    25

#define BUTTON_1         0
#else
#error "Please select the model of the board you want to use in main.cpp"
#endif

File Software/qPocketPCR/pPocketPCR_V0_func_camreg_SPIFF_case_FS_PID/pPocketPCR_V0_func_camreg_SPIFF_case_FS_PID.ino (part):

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#define PCLK_GPIO_NUM     22

#define EX_LEDS      25 //32
#define HEATER_PWM     4
#define FAN_PWM     12
#define HEATER_NTC  33 


#define LED1      6 // on MCP23008 Port Expander
#define CAM_PWR   5 // on MCP23008 Port Expander
#define CAM_PWDN   4 // on MCP23008 Port Expander
#define TFT_RST   3 // on MCP23008 Port Expander
#define TOUCH_RST   2 // on MCP23008 Port Expander
#define CAM_RST   1 // on MCP23008 Port Expander
#define TFT_BACKLIGHT   0 // on MCP23008 Port Expander

  
#define CASE_Main 1
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  mcp.pinMode(TFT_RST, OUTPUT); 
  mcp.digitalWrite(TFT_RST, HIGH); // TFT RESET,  LOW = RESET

  mcp.pinMode(TFT_BACKLIGHT, OUTPUT); 
  mcp.digitalWrite(TFT_BACKLIGHT, HIGH); // HIGH = BACKLIGHT ON

  mcp.pinMode(CAM_PWR, OUTPUT); 
  mcp.digitalWrite(CAM_PWR, LOW); // LOW = POWER ON

  mcp.pinMode(CAM_PWDN, OUTPUT); 
  mcp.digitalWrite(CAM_PWDN, 0); // 0: Normal mode / 1: Power down mode

  mcp.pinMode(CAM_RST, OUTPUT); 
  mcp.digitalWrite(CAM_RST, HIGH); // System reset input, active low

  mcp.pinMode(LED1, OUTPUT); // LED1
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  pinMode(EX_LEDS, OUTPUT); // Excitation LEDs
  analogWrite(EX_LEDS,50);   // turn the LED on (HIGH is the voltage level)

  pinMode(HEATER_PWM, OUTPUT); // Excitation LEDs
  digitalWrite(HEATER_PWM, LOW);


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  void setHeater(float temperature,float power)
{
  if (power==0) {
    pinMode(FAN_PWM, OUTPUT);
    pinMode(HEATER_PWM, OUTPUT);
    digitalWrite(FAN_PWM,LOW);
    digitalWrite(HEATER_PWM,LOW);
  }
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
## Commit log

2022-08-16 First commit of PCB files prototype.
2022-09-23 Various Demo and Developpement Code Beta
2025-11-05 first full release getting there
2025-11-05 First Full Release Getting there..
